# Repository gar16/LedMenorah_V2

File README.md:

# LedMenorah_V2
Second version of LED menorah with ATtiny2313. This second version is powered by two AAA batteries, the holders double as the stand. Firmware programming can be via ISP pins that are broken out.

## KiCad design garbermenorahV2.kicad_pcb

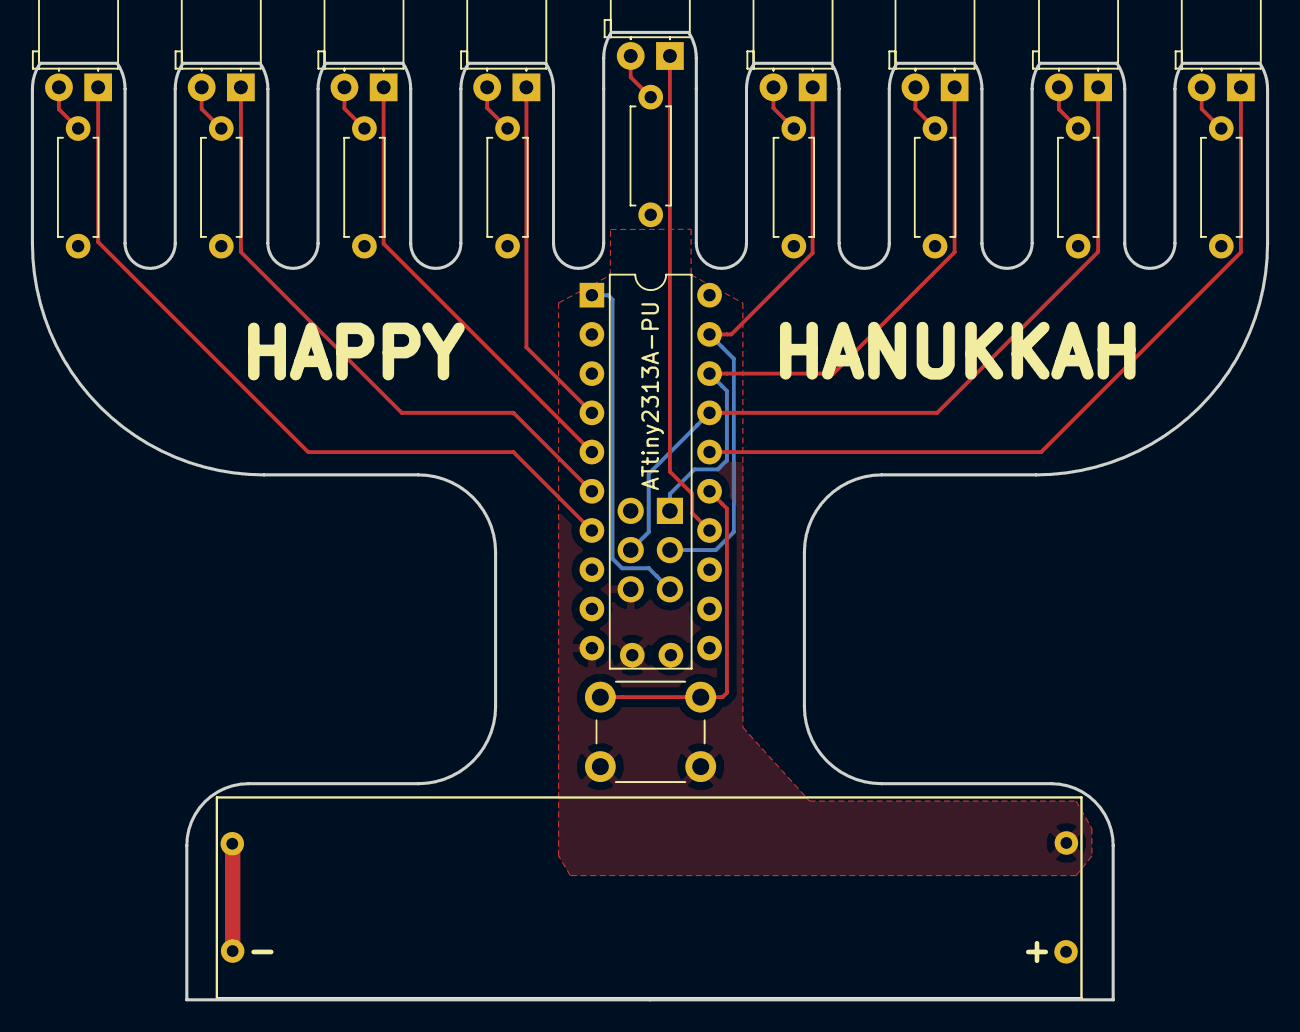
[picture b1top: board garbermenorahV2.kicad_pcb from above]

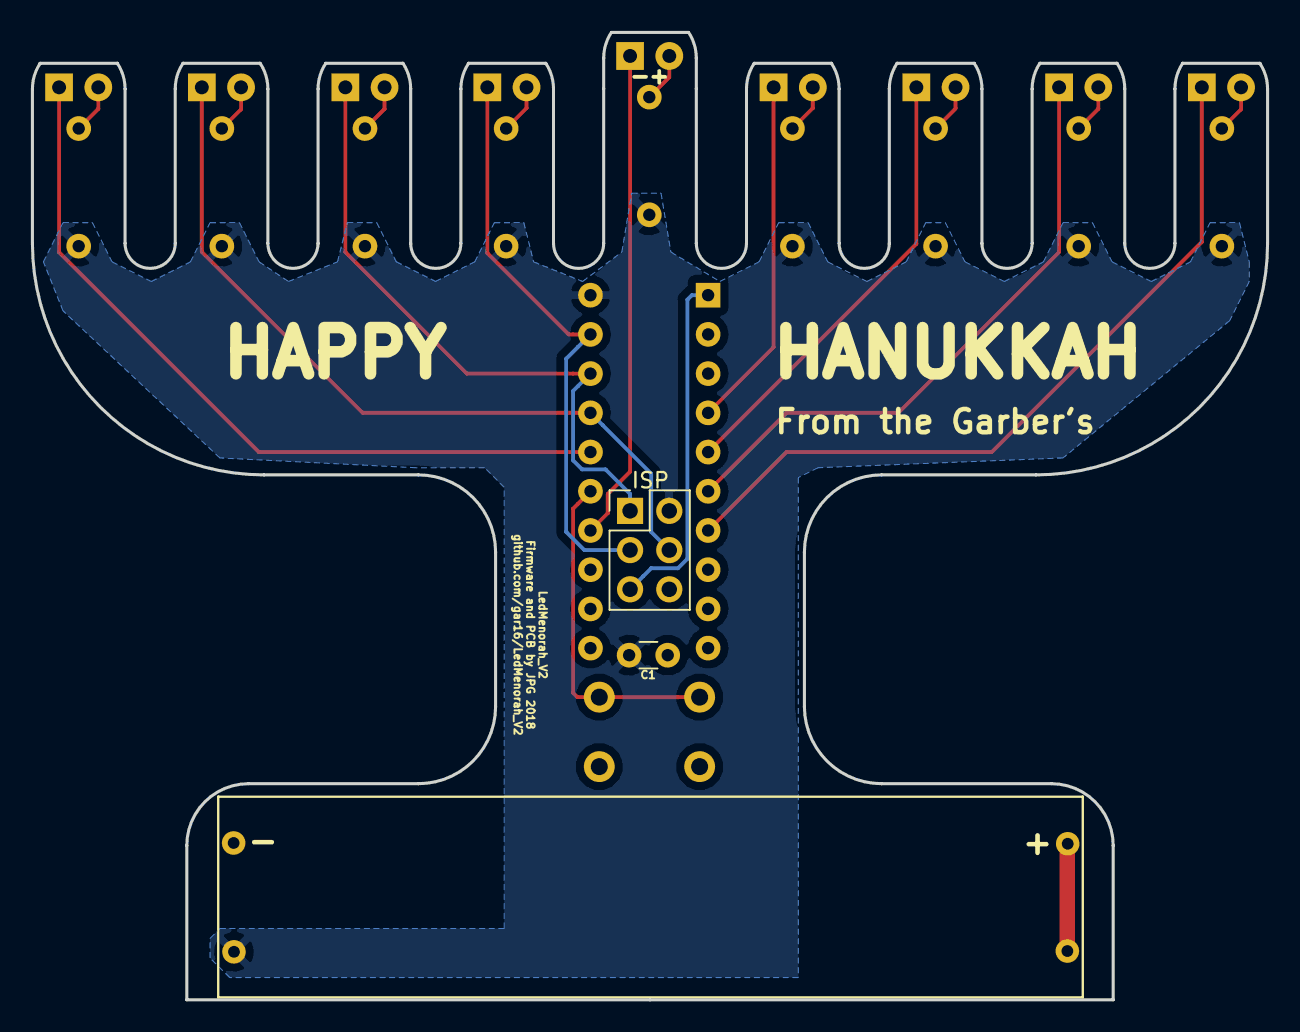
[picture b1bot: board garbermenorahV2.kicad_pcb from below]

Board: 2 copper layers, 80.0 x 62.7 mm, 24 parts (3 on the bottom side), 23 nets.

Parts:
BT1, BT2: AAA_Battery; AAA battery holder with leads
C1: 0.1uf; C_Disc_D3.0mm_W1.6mm_P2.50mm
J1: ISP; Pin_Header_Straight_2x03_Pitch2.54mm
MCU1: ATtiny2313A-PU; DIP-20_W7.62mm
R1, R2, R3, R4, R5, R6, R7, R8: 220; R_Axial_DIN0207_L6.3mm_D2.5mm_P7.62mm_Horizontal
Rshamash1: 220; R_Axial_DIN0207_L6.3mm_D2.5mm_P7.62mm_Horizontal
SW1: SW_SPST; SW_PUSH_6mm
eighthNLED1: LED; LED_D5.0mm_Horizontal_O1.27mm_Z3.0mm
fifthNLED1: LED; LED_D5.0mm_Horizontal_O1.27mm_Z3.0mm
firstNLED1: LED; LED_D5.0mm_Horizontal_O1.27mm_Z3.0mm
fourthNLED1: LED; LED_D5.0mm_Horizontal_O1.27mm_Z3.0mm
secondNLED1: LED; LED_D5.0mm_Horizontal_O1.27mm_Z3.0mm
seventhNLED1: LED; LED_D5.0mm_Horizontal_O1.27mm_Z3.0mm
shamash1: LED; LED_D5.0mm_Horizontal_O1.27mm_Z3.0mm
sixthNLED1: LED; LED_D5.0mm_Horizontal_O1.27mm_Z3.0mm
thirdNLED1: LED; LED_D5.0mm_Horizontal_O1.27mm_Z3.0mm

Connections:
GND: BT1.2, C1.1, J1.6, MCU1.10, SW1.2
unnamed: BT1.1, BT2.2
unnamed: MCU1.15, SW1.1
unnamed: R1.2, firstNLED1.2
unnamed: R2.2, secondNLED1.2
unnamed: R3.2, thirdNLED1.2
unnamed: R4.2, fourthNLED1.2
unnamed: R5.2, fifthNLED1.2
unnamed: R6.2, sixthNLED1.2
unnamed: R7.2, seventhNLED1.2
unnamed: R8.2, eighthNLED1.2
unnamed: Rshamash1.2, shamash1.2
RST: J1.5, MCU1.1
VCC: BT2.1, C1.2, J1.2, MCU1.20, R1.1, R2.1, R3.1, R4.1, R5.1, R6.1, R7.1, R8.1, Rshamash1.1
eighthN: MCU1.7, eighthNLED1.1
fifthN: MCU1.4, fifthNLED1.1
firstN: MCU1.16, firstNLED1.1
fourthN: J1.3, MCU1.19, fourthNLED1.1
secondN: J1.4, MCU1.17, secondNLED1.1
seventhN: MCU1.6, seventhNLED1.1
shamash: MCU1.14, shamash1.1
sixthN: MCU1.5, sixthNLED1.1
thirdN: J1.1, MCU1.18, thirdNLED1.1

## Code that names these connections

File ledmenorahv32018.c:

/*
 * ledmenorahv32018.c
 *
 * Created: 10/2018 11:50:45 AM
 * Author : Pin
 */ 


#define F_CPU 1000000UL //set cpu speed to 1mhz
//includes
#include <avr/io.h>
#include <util/delay.h>
#include <avr/interrupt.h>
#include <avr/sleep.h>
#include <stdlib.h>
//define ports by hex address so that they can be used in array
#define pportA 0x01B
#define pportB 0x018
#define pportD 0x012

#define shamashBrightness OCR0A //sets pwm duty cycle for shamash fading

//define nights to pins
#define eightN		PORTD3
#define seventhN	PORTD2
#define sixthN		PORTA0
#define fifthN		PORTA1
#define fourthN		PORTB7
#define thirdN		PORTB6
#define secondN		PORTB5
#define firstN		PORTB4
#define button		PORTB3

//arrays for pins and ports, consider moving to pgmspace flash later if room needed
const uint8_t led_ports [] = {0, pportB, pportB,  pportB, pportB,  pportA, pportA, pportD,   pportD}; 
const uint8_t led_pins [] =	{0, firstN, secondN, thirdN, fourthN, fifthN, sixthN, seventhN, eightN};

//variables
volatile uint8_t shamashFade = 0;
volatile uint8_t fadeRatecounter = 0;
uint8_t fadeAmount = 1;
volatile uint8_t buttonPressed = 0;
uint8_t nightNumber = 0;

//function declarations - consider move to header file later
void turn_off_led(int nightLed);
void turn_on_led(int nightLed);
void larson_scanner();
void setup_timer0_PWM();
void shamash_fader();
void clear_lights();
void light_menorah(int nightNumber);
void in_and_out();
void xmas_mode_for_z();
int main(void)
{
	DDRA =0xff;
	DDRB = 0xff;
	DDRD =0xff;
	PORTA = 0xff;
	PORTB = 0xff;
	PORTD = 0xff;
	DDRB &= ~(1<<DDB3);
	PORTB |= (1<<PORTB3);
	set_sleep_mode(SLEEP_MODE_PWR_DOWN); //sleep mode for battery saving, turns off cpu and all timers, will wake to pin change
	PCMSK |= (1<<PCINT3);//enable pin change interrupt on PB3
	GIMSK |= (1<<PCIE0);//interrupt mask enable
	setup_timer0_PWM();
	sei();
//
    while (1) 
    {//begin main while loop
		if (buttonPressed == 1){
			clear_lights();
			buttonPressed = 0;
			nightNumber++;
			
			if (nightNumber ==0){
				clear_lights();
			}
		
			if (nightNumber >0 && nightNumber <9){
				light_menorah(nightNumber);
			}
			if (nightNumber == 9){
				larson_scanner();
			}
			if (nightNumber == 10){
				in_and_out();
			}
			if (nightNumber == 11){
				xmas_mode_for_z();
			}
			if (nightNumber > 11){
				clear_lights();
				TCCR0A = 0;
				nightNumber = -1;
				sleep_mode();
				setup_timer0_PWM();
			}
	}//end main while loop
	}
}

void clear_lights(){
	for (int x = 0; x<9; x++){
		turn_off_led(x);
	}
}

void light_menorah(int nightNumber){
	for (int x = nightNumber; x>=0; x--){
		if(buttonPressed == 1){break;}// if the button is pressed drop out of the loop
		turn_on_led(x);
		_delay_ms(250);
	}
}

void larson_scanner(){
	
	while (buttonPressed == 0){
		for (int x = 0; x<9; x++){
			turn_on_led(x);
			turn_off_led(x-1);
			_delay_ms(50);
		}
		for (int x = 8; x>0; x--){
			turn_on_led(x);
			turn_off_led(x+1);
			_delay_ms(50);
		}
	}
	


}

void in_and_out(){
	uint8_t LtoR = 4;
	uint8_t RtoL = 5;
	
	while (buttonPressed == 0){
			while (LtoR > 0)
			{
				//4-1
				turn_on_led(LtoR);
				LtoR--;
				//5-8
				turn_on_led(RtoL);
				_delay_ms(75);
				RtoL++;
			}
			
			while (LtoR < 5)
			{
				//4-1
				turn_off_led(LtoR);
				LtoR++;
				//5-8
				turn_off_led(RtoL);
				_delay_ms(75);
				RtoL--;
			}
	}
}

void xmas_mode_for_z(){
	
	while (buttonPressed == 0){
		int8_t ranLightnum = rand() % 9;
		turn_on_led(ranLightnum);
		ranLightnum = rand() % 9;
		turn_off_led(ranLightnum);
		_delay_ms(500);
	}
}

void turn_on_led(int nightLed){
	
	_SFR_IO8(led_ports[nightLed]) &= ~(1<<led_pins[nightLed]);
	
}

void turn_off_led(int nightLed){
	
	_SFR_IO8(led_ports[nightLed]) |= (1<<led_pins[nightLed]);
}

void setup_timer0_PWM(){
	TCCR0A = (1 << COM0A1) | (1 << WGM00) | (1<<WGM01);  // fast PWM mode on pin OC0A

	TCCR0B = (1 << CS01);   // clock source = CLK/8, start PWM
	
	TIMSK |= (1<<OCIE0B);	//Timer/Counter0 Output Compare Match B Interrupt Enable
	shamashBrightness = 254;
	
}

void shamash_fader(){
	shamashBrightness = shamashBrightness + (fadeAmount);
	
	if (shamashBrightness == 0 || shamashBrightness == 255) {
		fadeAmount = -fadeAmount ;
	}
}

ISR (TIMER0_COMPB_vect){// timer interrupt for shamash fader

	if (fadeRatecounter>=5){
		shamash_fader();
		fadeRatecounter = 0;
	}
	fadeRatecounter++;
}

ISR (PCINT_B_vect){
	if(!(PINB & (1<<PINB3))){
		_delay_ms(150); //crude debounce, change to non-blocking later
		buttonPressed = 1;
	}
}

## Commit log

2018-09-26 Create ledmenorahinc.c
    Main C file for code
2018-09-26 Rename ledmenorahinc.c to ledmenorah_v2.c
2018-09-26 Rename ledmenorah_v2.c to ledmenorahinc.c
2018-09-28 Update ledmenorahinc.h
    changed pins for cleaner routing on board
2018-10-03 Update ledmenorahinc.h
    changed pins for better routing and do allow for UART communication
2018-10-18 Rename ledmenorahv32018.c to ledmenorah_v2_10_2018.c
2018-10-18 schematic created in Kicad
2018-10-18 PCB file in KiCad
2018-10-18 schematic file in KiCad
2018-10-18 Update ledmenorah_v2_10_2018.c
    added new patterns and changed timing
